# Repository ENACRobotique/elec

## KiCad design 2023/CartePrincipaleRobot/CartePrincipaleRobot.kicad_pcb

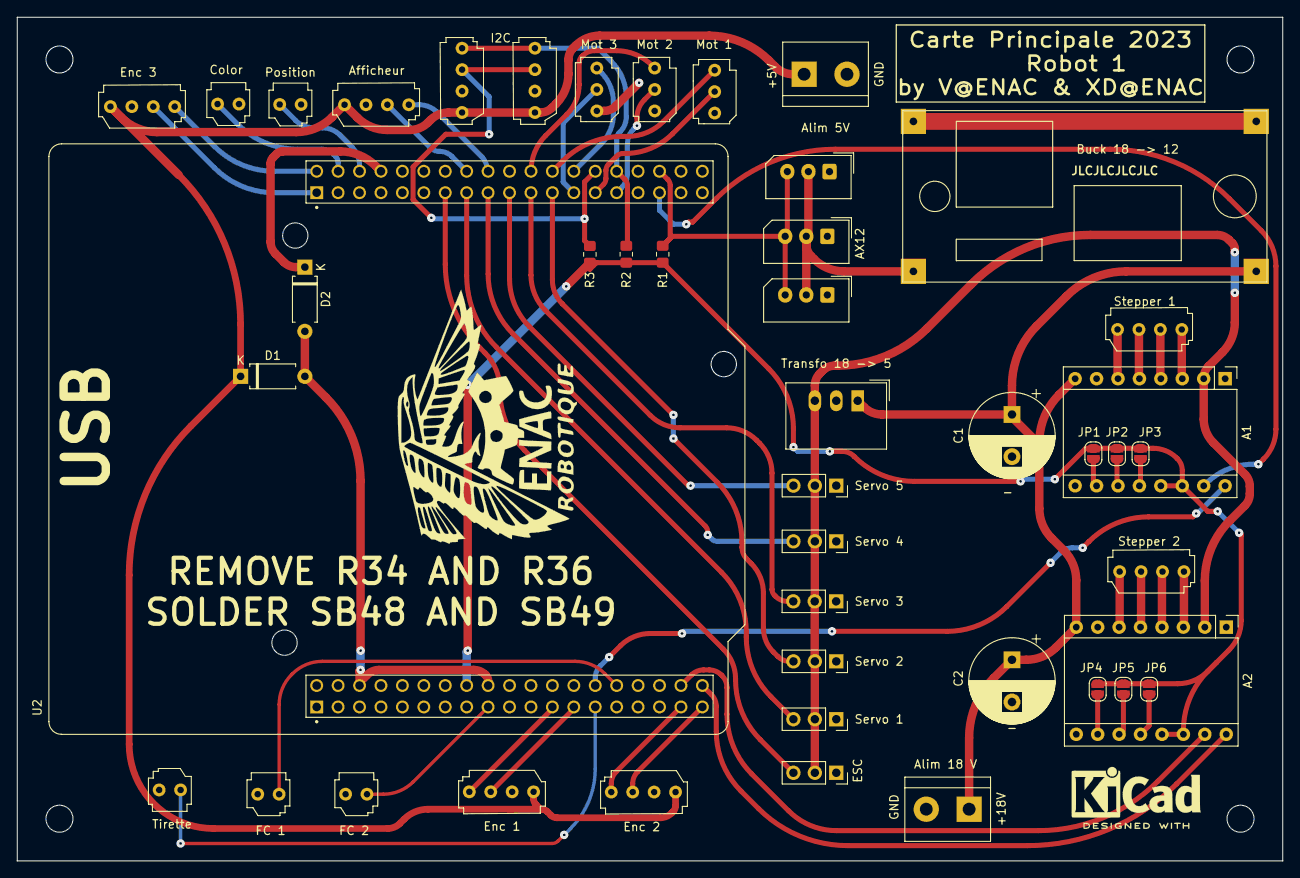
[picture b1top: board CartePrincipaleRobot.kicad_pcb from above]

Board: 2 copper layers, 150.0 x 100.0 mm, 45 parts (0 on the bottom side), 54 nets.

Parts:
A1, A2: Pololu_Breakout_A4988; Pololu_Breakout-16_15.2x20.3mm
AX12: Conn_01x03_Male; Molex_SPOX_5267-03A_1x03_P2.50mm_Vertical
Afficheur: Conn_01x04_Male; HE14_EMBASE_1x04
Alim 5V, Alim 18 V: Screw_Terminal_01x02; TerminalBlock_bornier-2_P5.08mm
Buck 18 -> 12: LM2596
C1, C2: 100µF; CP_Radial_D10.0mm_P5.00mm
Color: Conn_01x02_Male; HE14_EMBASE_1x02
D1, D2: DIODE; D_A-405_P7.62mm_Horizontal
ESC: Conn_01x03_Male; PinSocket_1x03_P2.54mm_Vertical
Enc 1, Enc 2, Enc 3: Conn_01x04_Male; HE14_EMBASE_1x04
FC 1, FC 2: Conn_01x02_Male; HE14_EMBASE_1x02
I2C: Conn_01x04_Male; HE14_EMBASE_1x04
J10, J11: Conn_01x03_Male; Molex_SPOX_5267-03A_1x03_P2.50mm_Vertical
J23: Conn_01x04_Male; HE14_EMBASE_1x04
JP1, JP2, JP3, JP4, JP5, JP6: SolderJumper_2_Open; SolderJumper-2_P1.3mm_Open_RoundedPad1.0x1.5mm
Mot 1, Mot 2, Mot 3: Conn_01x03_Male; HE14_EMBASE_1x03
Position: Conn_01x02_Male; HE14_EMBASE_1x02
R1: 1k; R_0805_2012Metric_Pad1.20x1.40mm_HandSolder
R2, R3: 2.2k; R_0805_2012Metric_Pad1.20x1.40mm_HandSolder
Servo 1, Servo 2, Servo 3, Servo 4, Servo 5: Conn_01x03_Male; PinSocket_1x03_P2.54mm_Vertical
Stepper 1, Stepper 2: Conn_01x04_Male; HE14_EMBASE_1x04
Tirette: Conn_01x02_Male; HE14_EMBASE_1x02
Transfo 18 -> 5: TSR_1-2450; Converter_DCDC_TRACO_TSR-1_THT
U2: NUCLEO-F476RG; ST_NUCLEO-F401RE

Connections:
5V_Logic: Afficheur.1, Alim 5V.1, D1.1 (K), Enc 1.1, Enc 2.1, Enc 3.1, I2C.1, J23.1
+3.3V: A1.13 (~RESET), A1.14 (~SLEEP), A2.13 (~RESET), A2.14 (~SLEEP), JP1.1 (A), JP2.1 (A), JP3.1 (A), JP4.1 (A), JP5.1 (A), JP6.1 (A), R1.1, R2.1, R3.1, U2.16 (+3V3)
+5V: A1.2 (VDD), A2.2 (VDD), ESC.2, Servo 1.2, Servo 2.2, Servo 3.2, Servo 4.2, Servo 5.2, Transfo 18 -> 5.3 (Vout)
+12V: AX12.2, Buck 18 -> 12.3 (OUT+), J10.2, J11.2
+18V: A1.8 (VMOT), A2.8 (VMOT), Alim 18 V.1, Buck 18 -> 12.1 (IN+), C1.1, C2.1, Transfo 18 -> 5.1 (Vin)
CLK_Afficheur: Afficheur.4, U2.56 (PB11)
Couleur: Color.1, U2.42 (PC6)
DIO_Afficheur: Afficheur.3, U2.54 (PB12)
ESC_PWM: ESC.3, U2.51 (PA6)
Enc1_A: Enc 1.3, U2.25 (PC14)
Enc1_B: Enc 1.4, U2.23 (PC13)
Enc2_A: Enc 2.3, U2.37 (PC3)
Enc2_B: Enc 2.4, U2.35 (PC2)
Enc3_A: Enc 3.3, U2.39 (PC9)
Enc3_B: Enc 3.4, U2.40 (PC8)
GND: A1.1 (GND), A1.7 (GND), A1.9 (~ENABLE), A2.1 (GND), A2.7 (GND), A2.9 (~ENABLE), AX12.1, Afficheur.2, Alim 5V.2, Alim 18 V.2, Buck 18 -> 12.2 (IN-), Buck 18 -> 12.4 (OUT-), C1.2, C2.2, Color.2, ESC.1, Enc 1.2, Enc 2.2, Enc 3.2, FC 1.1, FC 2.1, I2C.2, J10.1, J11.1, J23.2, Mot 1.1, Mot 2.1, Mot 3.1, Position.2, Servo 1.1, Servo 2.1, Servo 3.1, Servo 4.1, Servo 5.1, Tirette.2, Transfo 18 -> 5.2 (GND), U2.8 (GND), U2.19 (GND), U2.20 (GND), U2.22 (GND), U2.47 (GND), U2.58 (GND), U2.70 (AGND)
I2C_SCL: I2C.4, J23.4, R2.2, U2.68 (PB13)
I2C_SDA: I2C.3, J23.3, R3.2, U2.66 (PB14)
MOT1_DIR: Mot 1.3, U2.62 (PB1)
MOT1_PWM: Mot 1.2, U2.65 (PB4)
MOT2_DIR: Mot 2.3, U2.60 (PB2)
MOT2_PWM: Mot 2.2, U2.67 (PB5)
MOT3_DIR: Mot 3.3, U2.64 (PB15)
MOT3_PWM: Mot 3.2, U2.63 (PB10)
unnamed: A1.3 (1B), Stepper 1.4
unnamed: A1.4 (1A), Stepper 1.3
unnamed: A1.5 (2A), Stepper 1.2
unnamed: A1.6 (2B), Stepper 1.1
unnamed: A1.10 (MS1), JP1.2 (B)
unnamed: A1.11 (MS2), JP2.2 (B)
unnamed: A1.12 (MS3), JP3.2 (B)
unnamed: A2.3 (1B), Stepper 2.4
unnamed: A2.4 (1A), Stepper 2.3
unnamed: A2.5 (2A), Stepper 2.2
unnamed: A2.6 (2B), Stepper 2.1
unnamed: A2.10 (MS1), JP4.2 (B)
unnamed: A2.11 (MS2), JP5.2 (B)
unnamed: A2.12 (MS3), JP6.2 (B)
unnamed: D1.2 (A), D2.2 (A), U2.6 (E5V), U2.18 (+5V)
unnamed: D2.1 (K), U2.46 (U5V)
Position: Position.1, U2.44 (PC5)
Servo1: Servo 1.3, U2.53 (PA7)
Servo2: Servo 2.3, U2.61 (PA8)
Servo3: Servo 3.3, U2.59 (PA9)
Servo4: Servo 4.3, U2.55 (PB6)
Servo5: Servo 5.3, U2.57 (PC7)
Signal_AX12A: AX12.3, J10.3, J11.3, R1.2, U2.72 (PC4)
Stepper1_FinCourse: FC 1.2, U2.30 (PA1)
Stepper1_STP: A1.15 (STEP), U2.71 (PA10)
Stepper1_dir: A1.16 (DIR), U2.28 (PA0)
Stepper2_FinCourse: FC 2.2, U2.17 (PA15)
Stepper2_STP: A2.15 (STEP), U2.36 (PC1)
Stepper2_dir: A2.16 (DIR), U2.38 (PC0)
Tirette: Tirette.1, U2.27 (PC15)

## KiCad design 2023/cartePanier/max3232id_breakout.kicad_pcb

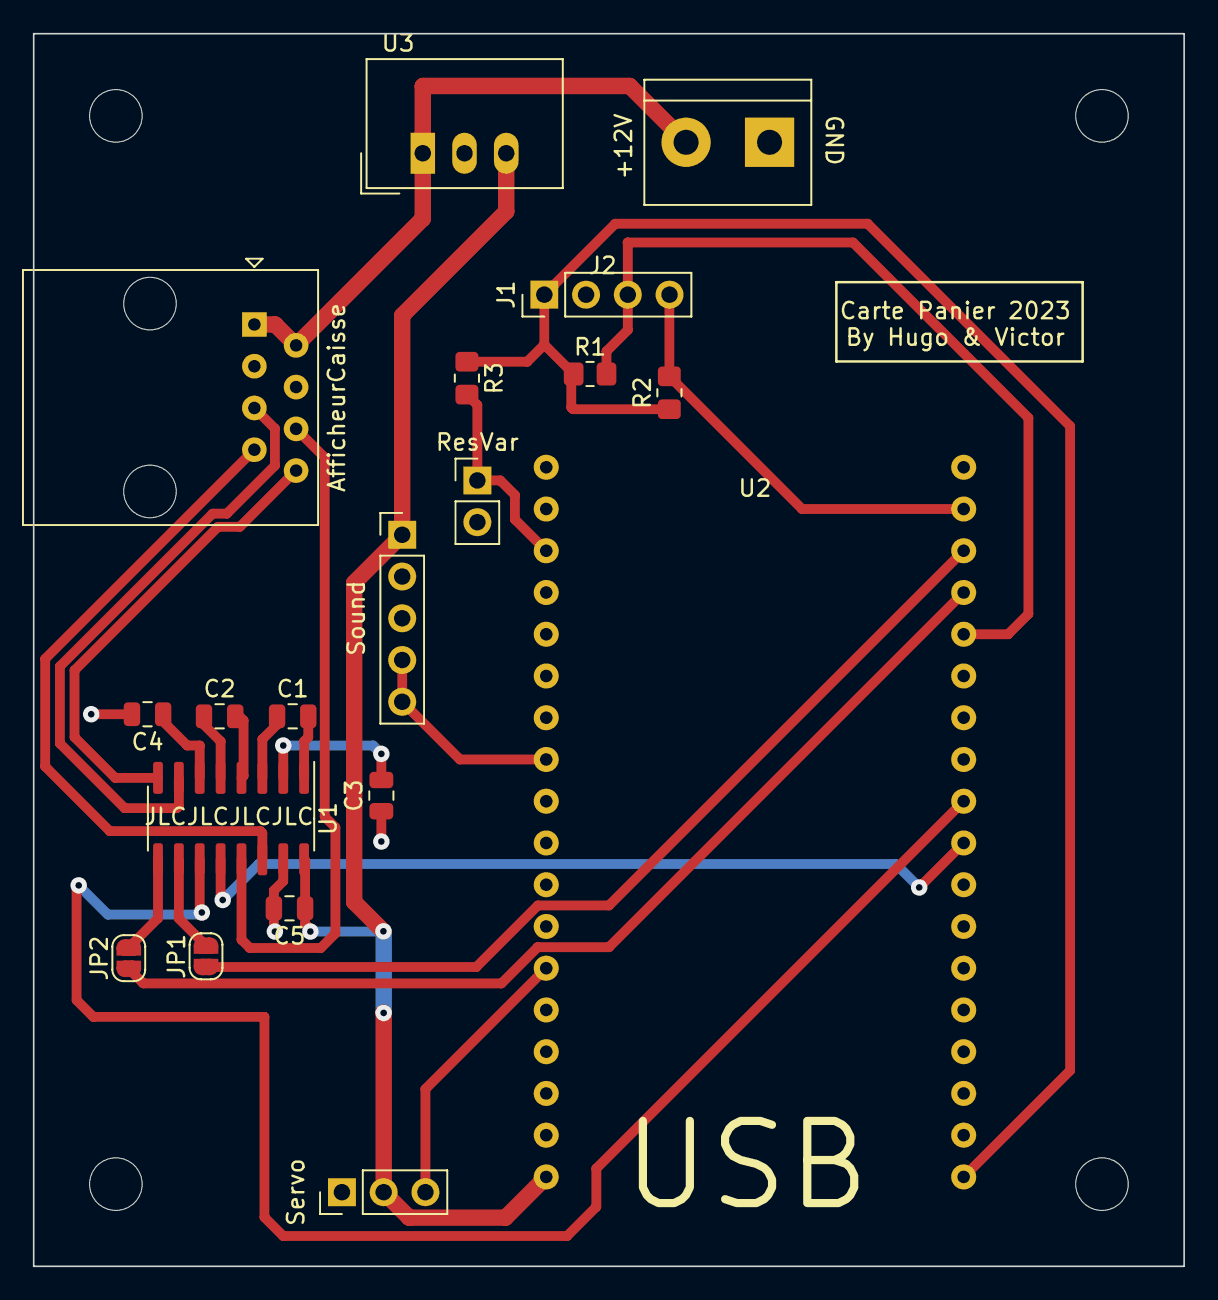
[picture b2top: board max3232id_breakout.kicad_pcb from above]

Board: 2 copper layers, 70.0 x 75.0 mm, 19 parts (0 on the bottom side), 25 nets.

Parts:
AfficheurCaisse: RJ45; RJ45_Amphenol_54602-x08_Horizontal
C1, C2, C3, C4, C5: 100n; C_0805_2012Metric
J1: Conn_01x04_Male; PinHeader_1x04_P2.54mm_Vertical
J2: Conn_01x02; TerminalBlock_bornier-2_P5.08mm
JP1, JP2: SolderJumper_2_Open; SolderJumper-2_P1.3mm_Open_RoundedPad1.0x1.5mm
R1, R2: R; R_0805_2012Metric_Pad1.20x1.40mm_HandSolder
R3: A Calculer; R_0805_2012Metric_Pad1.20x1.40mm_HandSolder
ResVar: Conn_01x02_Male; PinHeader_1x02_P2.54mm_Vertical
Servo: Conn_01x03_Male; PinHeader_1x03_P2.54mm_Vertical
Sound: Conn_01x05_Male; PinHeader_1x05_P2.54mm_Vertical
U1: MAX3232; SOIC-16_3.9x9.9mm_P1.27mm
U2: DOIT-ESP32-DEVKIT-V1; ESP32-DOIT-DEVKIT
U3: TSR_1-2450; Converter_DCDC_TRACO_TSR-1_THT

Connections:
+3.3V: J1.1, R1.1, R2.1, R3.1, U2.19 (3V3)
+5V: C5.1, Servo.2, Sound.1, U1.16 (VCC), U2.18 (VIN), U3.3 (Vout)
+12V: AfficheurCaisse.1, AfficheurCaisse.2, J2.2, U3.1 (Vin)
GND: AfficheurCaisse.3, AfficheurCaisse.4, C3.1, C4.2, C5.2, J1.2, J2.1, ResVar.2, Servo.1, Sound.2, Sound.3, U1.15 (GND), U2.17 (GND), U3.2 (GND)
I2C_SCL: J1.4, R2.2, U2.35 (GPIO22_I2C-SCL)
I2C_SDA: J1.3, R1.2, U2.32 (GPIO21_I2C-SDA)
LOGIC_IN1: U1.11 (T1IN), U2.28 (GPIO17_UART2-TX)
LOGIC_IN2: JP1.2 (B), U1.10 (T2IN)
LOGIC_OUT1: U1.12 (R1OUT), U2.27 (GPIO16_UART2-RX)
LOGIC_OUT2: JP2.2 (B), U1.9 (R2OUT)
MesurResVar: R3.2, ResVar.1, U2.3 (GPIO39_ADC1-CH3_SENS-VN_RTC-GPIO3)
unnamed: C1.1, U1.3 (C1-)
unnamed: C1.2, U1.1 (C1+)
unnamed: C2.1, U1.5 (C2-)
unnamed: C2.2, U1.4 (C2+)
unnamed: C3.2, U1.2 (VS+)
unnamed: C4.1, U1.6 (VS-)
unnamed: JP1.1 (A), U2.34 (GPIO1_UART0-TX)
unnamed: JP2.1 (A), U2.33 (GPIO3__UART0-RX)
RS232_IN1: AfficheurCaisse.6, U1.13 (R1IN)
RS232_IN2: AfficheurCaisse.8, U1.8 (R2IN)
RS232_OUT1: AfficheurCaisse.7, U1.14 (T1OUT)
RS232_OUT2: AfficheurCaisse.5, U1.7 (T2OUT)
SERVO: Servo.3, U2.13 (GPIO13_ADC2-CH4_HSPI-MOSI_RTC-GPIO14)
SOUND: Sound.4, Sound.5, U2.8 (GPIO25_ADC2-CH8_DAC1_RTC-GPIO6)

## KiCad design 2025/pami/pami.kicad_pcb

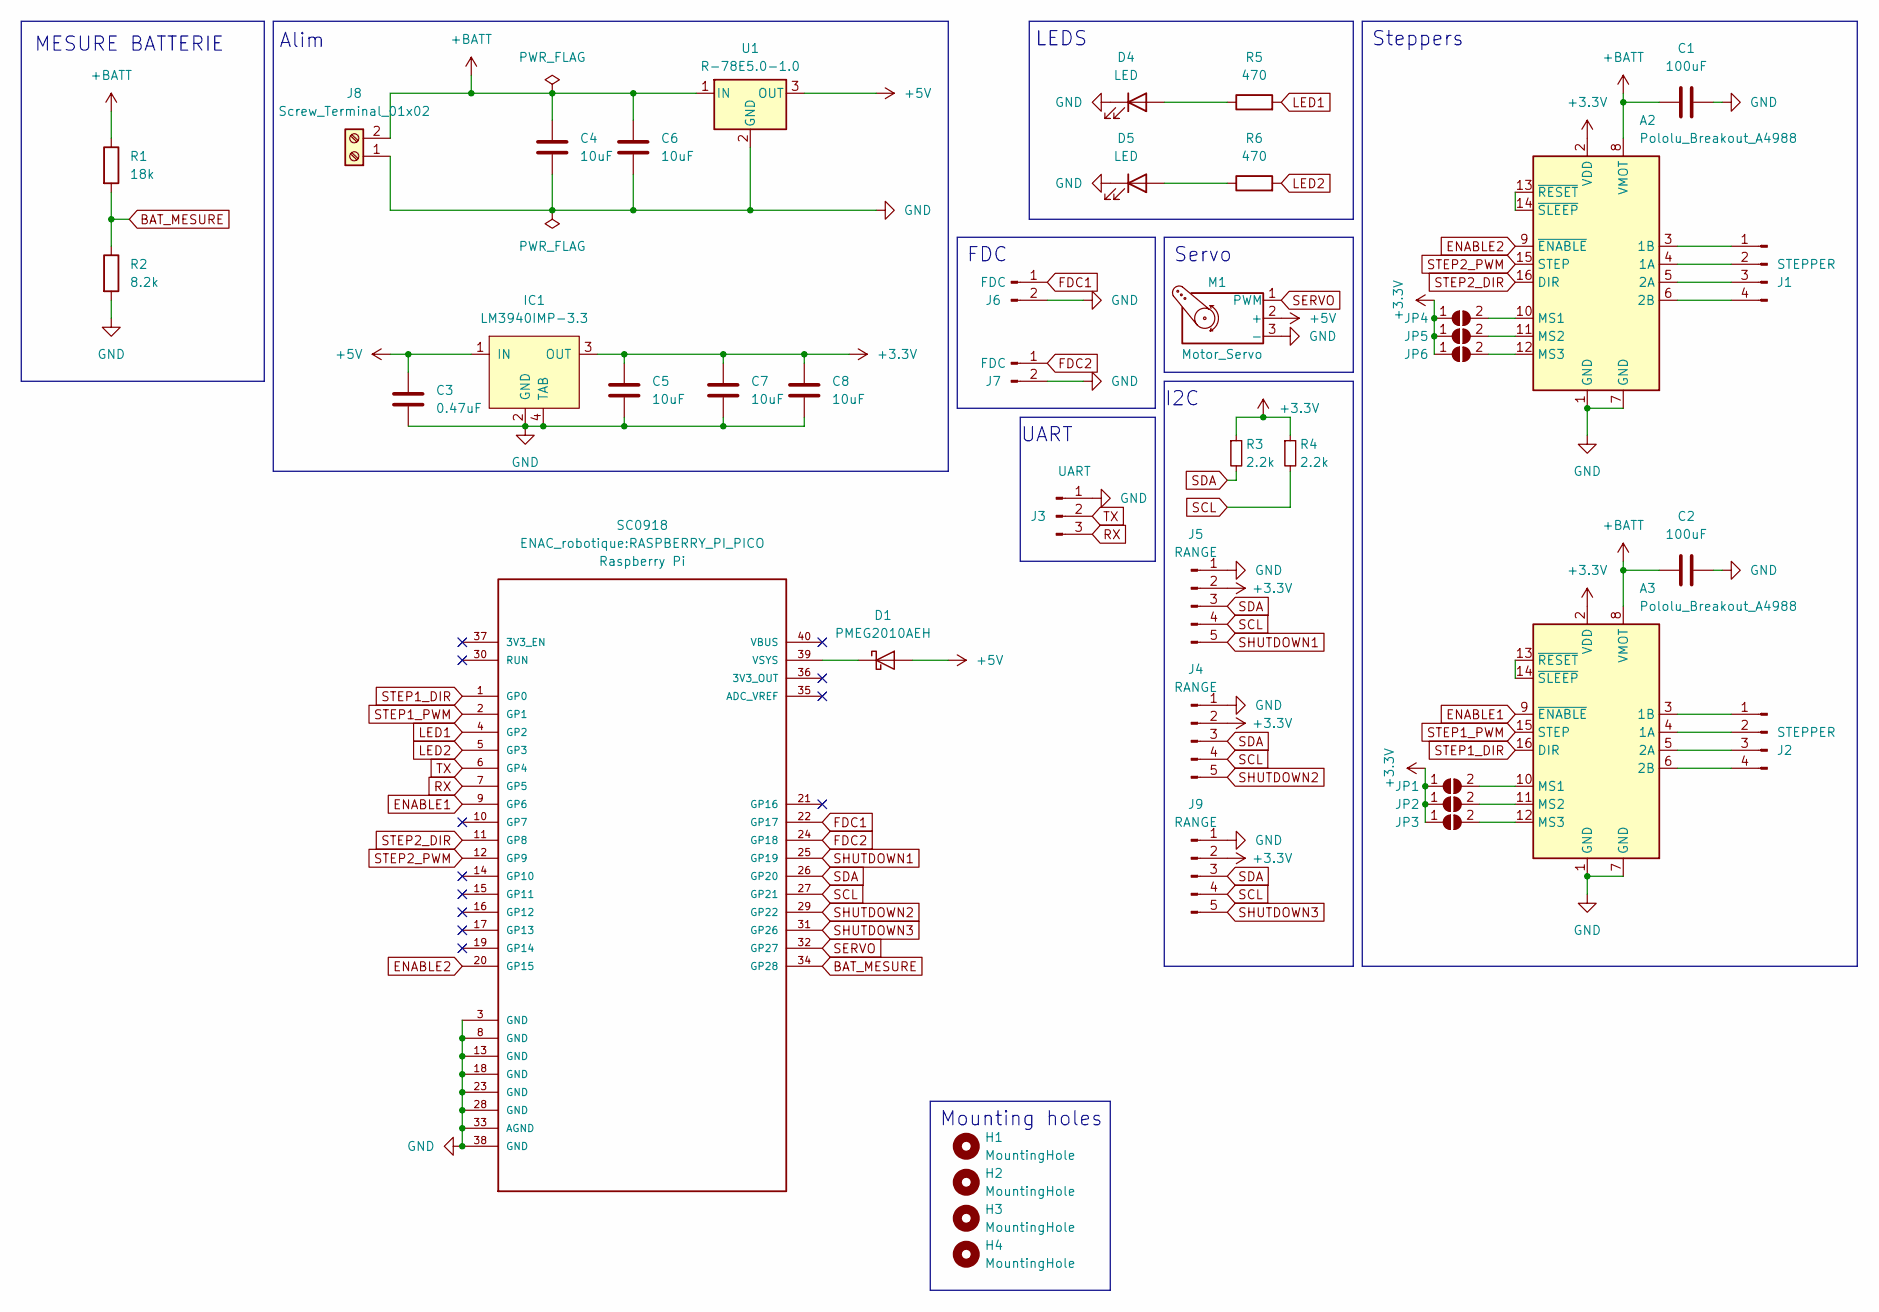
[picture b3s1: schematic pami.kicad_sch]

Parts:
A1: SC0918; RASPBERRY_PI_PICO; PARTREV 1.6
A2, A3: Pololu_Breakout_A4988; Pololu_Breakout-16_15.2x20.3mm
C1, C2: 100uF; CP_Elec_10x12.5
C3: 0.47uF; C_0805_2012Metric
C4, C5, C6, C7, C8: 10uF; C_0805_2012Metric
D1: PMEG2010AEH; D_SOD-123F
D4, D5: LED; LED_0603_1608Metric
H1, H2, H3, H4: MountingHole; MountingHole_3.2mm_M3
IC1: LM3940IMP-3.3; LM3940IMP
J1, J2: STEPPER; PinHeader_1x04_P2.54mm_Vertical
J3: UART; PinHeader_1x03_P2.54mm_Vertical
J4, J5, J9: RANGE; Molex_PicoBlade_53398-0571_1x05-1MP_P1.25mm_Vertical
J6, J7: FDC; PinHeader_1x02_P2.54mm_Vertical
J8: Screw_Terminal_01x02; TerminalBlock_bornier-2_P5.08mm
JP1, JP2, JP3, JP4, JP5, JP6: SolderJumper_2_Open; SolderJumper-2_P1.3mm_Open_TrianglePad1.0x1.5mm
M1: Motor_Servo; PinHeader_1x03_P2.54mm_Vertical
R1: 18k; R_0603_1608Metric
R2: 8.2k; R_0603_1608Metric
R3, R4: 2.2k; R_0805_2012Metric
R5, R6: 470; R_0603_1608Metric
U1: R-78E5.0-1.0; Converter_DCDC_RECOM_R-78E-0.5_THT

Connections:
+3.3V: A2.2 (VDD), A3.2 (VDD), C5.1, C7.1, C8.1, IC1.3 (OUT), J4.2, J5.2, J9.2, JP1.1 (A), JP2.1 (A), JP3.1 (A), JP4.1 (A), JP5.1 (A), JP6.1 (A), R3.1, R4.1
+5V: C3.1, D1.2 (A), IC1.1 (IN), M1.2 (+), U1.3 (OUT); also elsewhere on the board
+BATT: A2.8 (VMOT), A3.8 (VMOT), C1.1, C2.1, C4.2, C6.2, J8.2, R1.1, U1.1 (IN); also elsewhere on the board
BAT_MESURE: A1.34 (GP28), R1.2, R2.1
ENABLE1: A1.9 (GP6), A3.9 (~ENABLE)
ENABLE2: A1.20 (GP15), A2.9 (~ENABLE)
FDC1: A1.22 (GP17), J6.1; also elsewhere on the board
FDC2: A1.24 (GP18), J7.1; also elsewhere on the board
GND: A1.3 (GND), A1.8 (GND), A1.13 (GND), A1.18 (GND), A1.23 (GND), A1.28 (GND), A1.33 (AGND), A1.38 (GND), A2.1 (GND), A2.7 (GND), A3.1 (GND), A3.7 (GND), C1.2, C2.2, C3.2, C4.1, C5.2, C6.1, C7.2, C8.2, D4.1 (K), D5.1 (K), IC1.2 (GND), IC1.4 (TAB), J3.1, J4.1, J5.1, J6.2, J7.2, J8.1, J9.1, M1.3 (-), R2.2, U1.2 (GND); also elsewhere on the board
LED1: A1.4 (GP2), R5.2
LED2: A1.5 (GP3), R6.2
unnamed: A1.39 (VSYS), D1.1 (K)
unnamed: A2.4 (1A), J1.2
unnamed: A2.3 (1B), J1.1
unnamed: A2.5 (2A), J1.3
unnamed: A2.6 (2B), J1.4
unnamed: A2.10 (MS1), JP4.2 (B)
unnamed: A2.11 (MS2), JP5.2 (B)
unnamed: A2.12 (MS3), JP6.2 (B)
unnamed: A2.13 (~RESET), A2.14 (~SLEEP)
unnamed: A3.4 (1A), J2.2
unnamed: A3.3 (1B), J2.1
unnamed: A3.5 (2A), J2.3
unnamed: A3.6 (2B), J2.4
unnamed: A3.10 (MS1), JP1.2 (B)
unnamed: A3.11 (MS2), JP2.2 (B)
unnamed: A3.12 (MS3), JP3.2 (B)
unnamed: A3.13 (~RESET), A3.14 (~SLEEP)
unnamed: D4.2 (A), R5.1
unnamed: D5.2 (A), R6.1
RX: A1.7 (GP5), J3.3
SCL: A1.27 (GP21), J4.4, J5.4, J9.4, R4.2
SDA: A1.26 (GP20), J4.3, J5.3, J9.3, R3.2
SERVO: A1.32 (GP27), M1.1 (PWM)
SHUTDOWN1: A1.25 (GP19), J5.5
SHUTDOWN2: A1.29 (GP22), J4.5
SHUTDOWN3: A1.31 (GP26), J9.5
STEP1_DIR: A1.1 (GP0), A3.16 (DIR)
STEP1_PWM: A1.2 (GP1), A3.15 (STEP)
STEP2_DIR: A1.11 (GP8), A2.16 (DIR)
STEP2_PWM: A1.12 (GP9), A2.15 (STEP)
TX: A1.6 (GP4), J3.2

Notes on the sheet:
Steppers
FDC
I2C
LEDS
Alim
Servo
UART
Mounting holes
MESURE BATTERIE

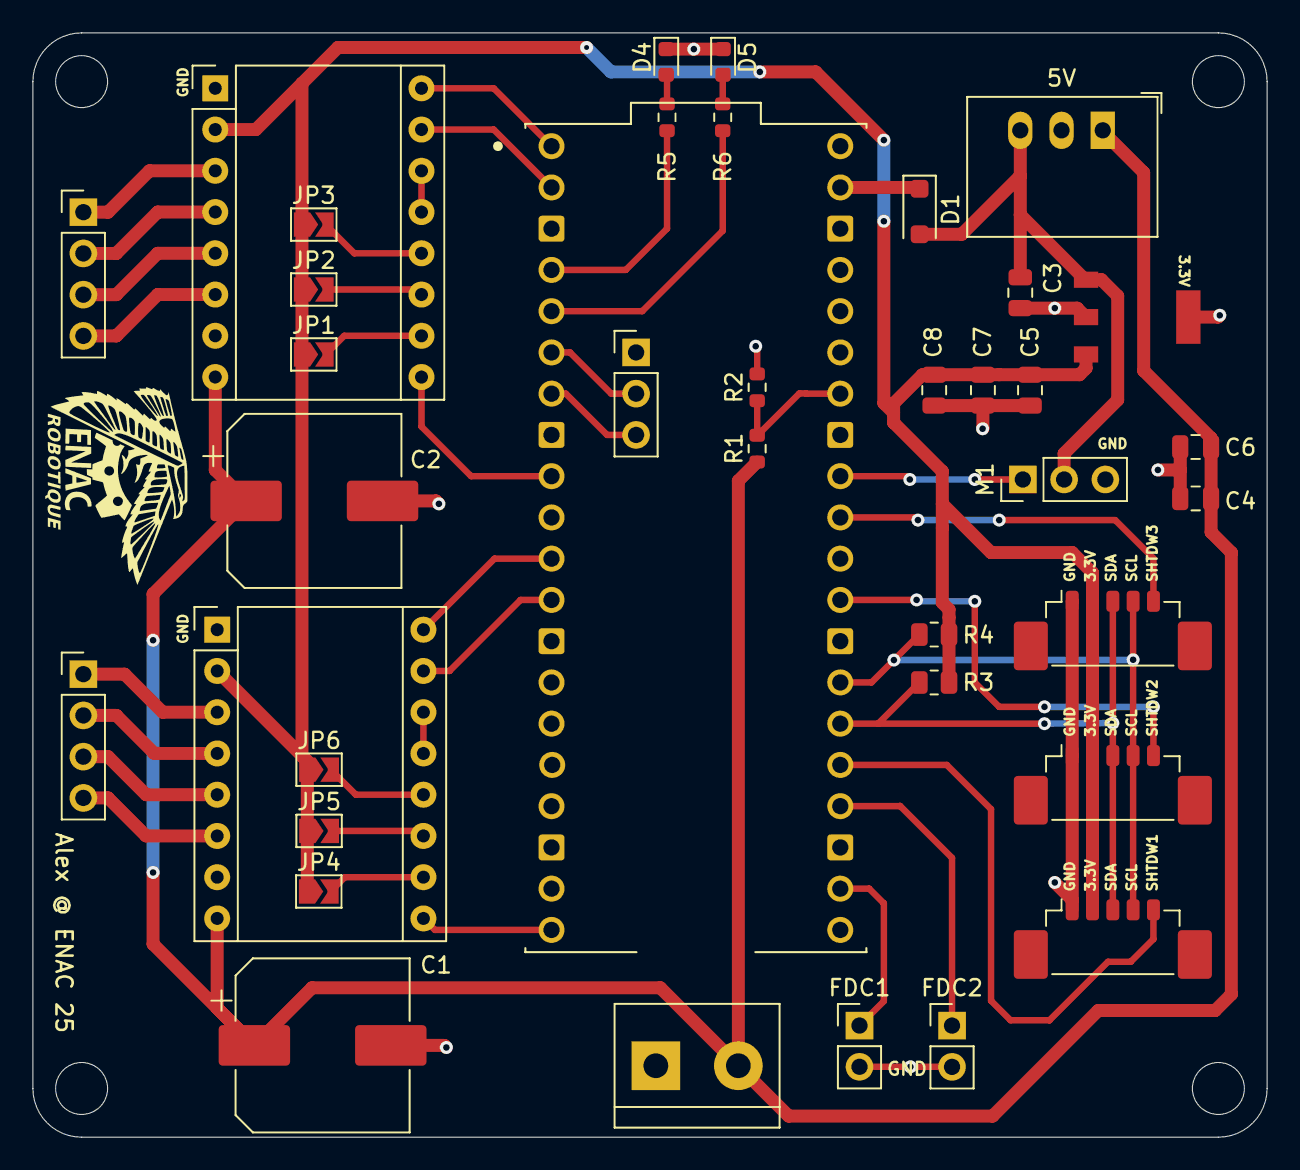
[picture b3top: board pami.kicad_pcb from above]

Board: 2 copper layers, 76.0 x 68.0 mm, 42 parts (0 on the bottom side), 42 nets.

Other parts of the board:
5V: R-78E5.0-1.0; Converter_DCDC_RECOM_R-78E-0.5_THT
FDC1, FDC2: FDC; PinHeader_1x02_P2.54mm_Vertical

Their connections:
+5V: 5V.3 (OUT); also elsewhere on the board
+BATT: 5V.1 (IN); also elsewhere on the board
FDC1: FDC1.1; also elsewhere on the board
FDC2: FDC2.1; also elsewhere on the board
GND: 5V.2 (GND), FDC1.2, FDC2.2; also elsewhere on the board

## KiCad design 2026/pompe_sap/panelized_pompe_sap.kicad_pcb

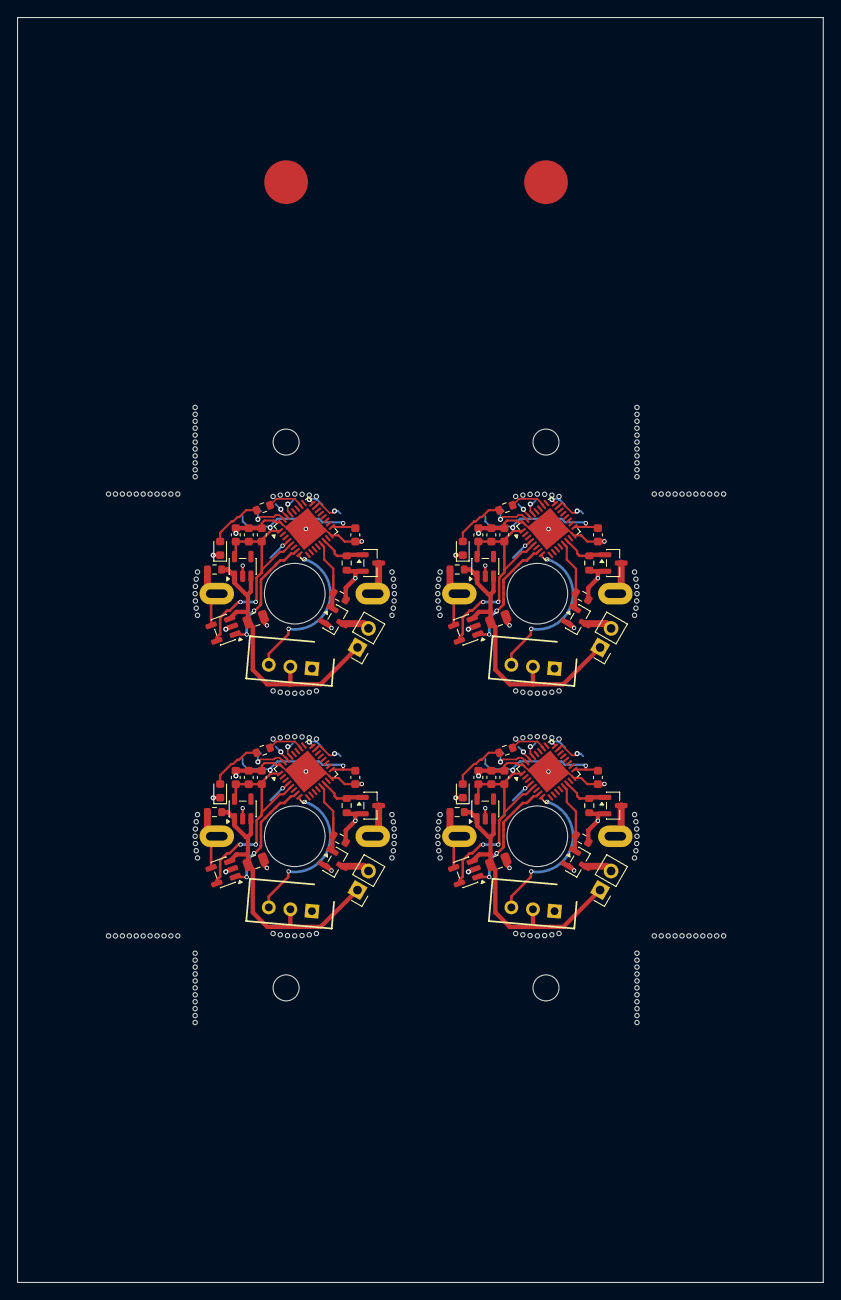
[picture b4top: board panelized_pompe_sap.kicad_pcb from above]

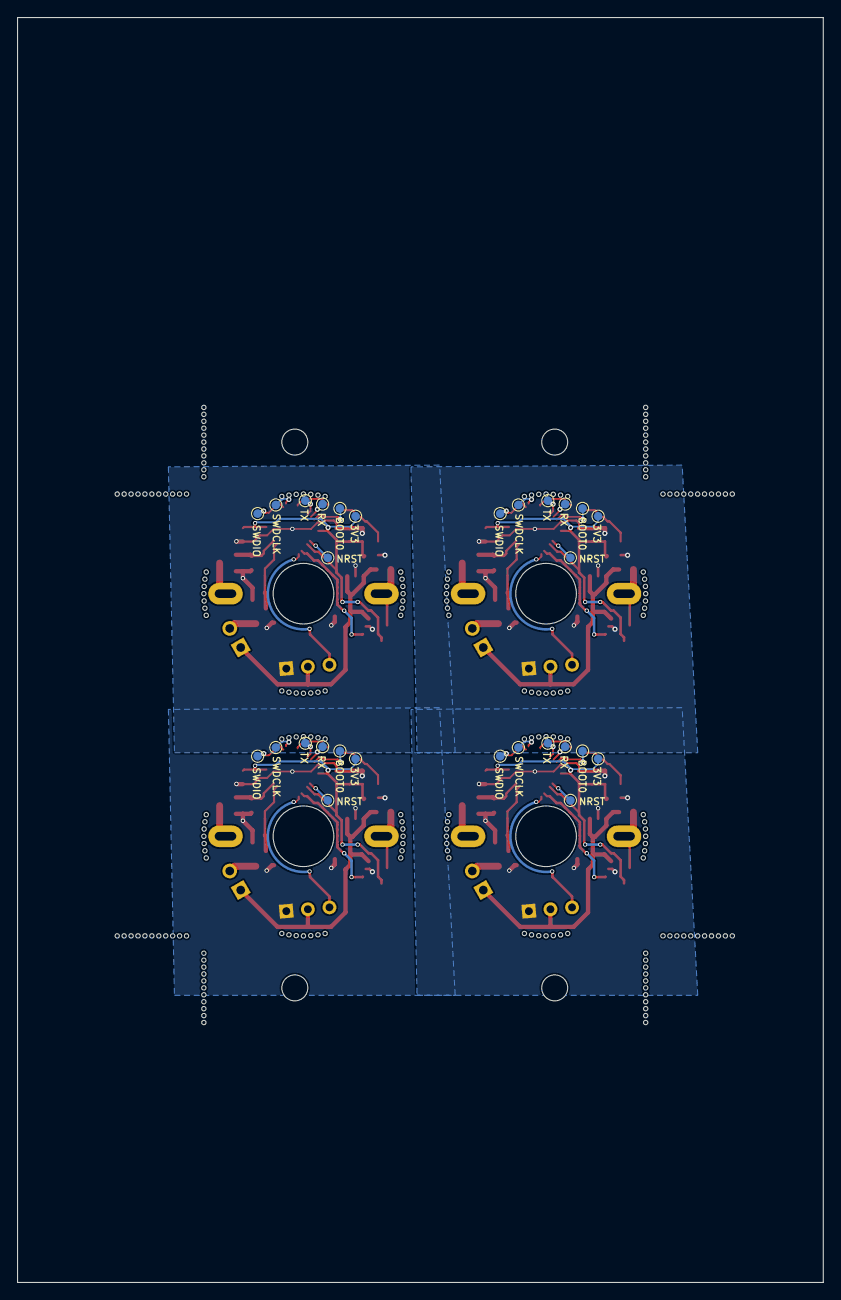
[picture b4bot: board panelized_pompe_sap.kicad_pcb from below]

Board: 2 copper layers, 93.0 x 146.0 mm, 304 parts (28 on the bottom side), 72 nets.

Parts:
C1, C1#2, C1#3, C1#4: C 1uf; C_0805_2012Metric
C2, C2#2, C2#3, C2#4: C 1uf; C_0603_1608Metric
C3, C3#2, C3#3, C3#4: 4U7; C_0603_1608Metric
C4, C4#2, C4#3, C4#4, C5, C5#2, C5#3, C5#4: 100n; C_0603_1608Metric
D1, D1#2, D1#3, D1#4: LED; LED_0603_1608Metric
J1, J1#2, J1#3, J1#4: Conn_01x02_Pin; PinHeader_1x02_P2.54mm_Vertical
J2, J2#2, J2#3, J2#4: 22-03-5035; SHDR3W70P0X250_1X3_990X490X590P
KiKit_MB_1_1, KiKit_MB_1_2, KiKit_MB_1_3, KiKit_MB_1_4, KiKit_MB_1_5, KiKit_MB_1_6, KiKit_MB_1_7, KiKit_MB_2_1, KiKit_MB_2_2, KiKit_MB_2_3, KiKit_MB_2_4, KiKit_MB_2_5, KiKit_MB_2_6, KiKit_MB_2_7, KiKit_MB_3_1, KiKit_MB_3_2, KiKit_MB_3_3, KiKit_MB_3_4, KiKit_MB_3_5, KiKit_MB_3_6, KiKit_MB_3_7, KiKit_MB_4_1, KiKit_MB_4_2, KiKit_MB_4_3, KiKit_MB_4_4, KiKit_MB_4_5, KiKit_MB_4_6, KiKit_MB_4_7, KiKit_MB_5_1, KiKit_MB_5_2, KiKit_MB_5_3, KiKit_MB_5_4, KiKit_MB_5_5, KiKit_MB_5_6, KiKit_MB_5_7, KiKit_MB_6_1, KiKit_MB_6_2, KiKit_MB_6_3, KiKit_MB_6_4, KiKit_MB_6_5, KiKit_MB_6_6, KiKit_MB_6_7, KiKit_MB_7_1, KiKit_MB_7_2, KiKit_MB_7_3, KiKit_MB_7_4, KiKit_MB_7_5, KiKit_MB_7_6, KiKit_MB_7_7, KiKit_MB_8_1, KiKit_MB_8_2, KiKit_MB_8_3, KiKit_MB_8_4, KiKit_MB_8_5, KiKit_MB_8_6, KiKit_MB_8_7, KiKit_MB_9_1, KiKit_MB_9_2, KiKit_MB_9_3, KiKit_MB_9_4, KiKit_MB_9_5, KiKit_MB_9_6, KiKit_MB_9_7, KiKit_MB_10_1, KiKit_MB_10_2, KiKit_MB_10_3, KiKit_MB_10_4, KiKit_MB_10_5, KiKit_MB_10_6, KiKit_MB_10_7, KiKit_MB_11_1, KiKit_MB_11_2, KiKit_MB_11_3, KiKit_MB_11_4, KiKit_MB_11_5, KiKit_MB_11_6, KiKit_MB_11_7, KiKit_MB_12_1, KiKit_MB_12_2, KiKit_MB_12_3, KiKit_MB_12_4, KiKit_MB_12_5, KiKit_MB_12_6, KiKit_MB_12_7, KiKit_MB_13_1, KiKit_MB_13_2, KiKit_MB_13_3, KiKit_MB_13_4, KiKit_MB_13_5, KiKit_MB_13_6, KiKit_MB_13_7, KiKit_MB_14_1, KiKit_MB_14_2, KiKit_MB_14_3, KiKit_MB_14_4, KiKit_MB_14_5, KiKit_MB_14_6, KiKit_MB_14_7, KiKit_MB_15_1, KiKit_MB_15_2, KiKit_MB_15_3, KiKit_MB_15_4, KiKit_MB_15_5, KiKit_MB_15_6, KiKit_MB_15_7, KiKit_MB_16_1, KiKit_MB_16_2, KiKit_MB_16_3, KiKit_MB_16_4, KiKit_MB_16_5, KiKit_MB_16_6, KiKit_MB_16_7, KiKit_MB_17_1, KiKit_MB_17_2, KiKit_MB_17_3, KiKit_MB_17_4, KiKit_MB_17_5, KiKit_MB_17_6, KiKit_MB_17_7, KiKit_MB_17_8, KiKit_MB_17_9, KiKit_MB_17_10, KiKit_MB_17_11, KiKit_MB_18_1, KiKit_MB_18_2, KiKit_MB_18_3, KiKit_MB_18_4, KiKit_MB_18_5, KiKit_MB_18_6, KiKit_MB_18_7, KiKit_MB_18_8, KiKit_MB_18_9, KiKit_MB_18_10, KiKit_MB_18_11, KiKit_MB_19_1, KiKit_MB_19_2, KiKit_MB_19_3, KiKit_MB_19_4, KiKit_MB_19_5, KiKit_MB_19_6, KiKit_MB_19_7, KiKit_MB_19_8, KiKit_MB_19_9, KiKit_MB_19_10, KiKit_MB_19_11, KiKit_MB_20_1, KiKit_MB_20_2, KiKit_MB_20_3, KiKit_MB_20_4, KiKit_MB_20_5, KiKit_MB_20_6, KiKit_MB_20_7, KiKit_MB_20_8, KiKit_MB_20_9, KiKit_MB_20_10, KiKit_MB_20_11, KiKit_MB_21_1, KiKit_MB_21_2, KiKit_MB_21_3, KiKit_MB_21_4, KiKit_MB_21_5, KiKit_MB_21_6, KiKit_MB_21_7, KiKit_MB_21_8, KiKit_MB_21_9, KiKit_MB_21_10, KiKit_MB_21_11, KiKit_MB_22_1, KiKit_MB_22_2, KiKit_MB_22_3, KiKit_MB_22_4, KiKit_MB_22_5, KiKit_MB_22_6, KiKit_MB_22_7, KiKit_MB_22_8, KiKit_MB_22_9, KiKit_MB_22_10, KiKit_MB_22_11, KiKit_MB_23_1, KiKit_MB_23_2, KiKit_MB_23_3, KiKit_MB_23_4, KiKit_MB_23_5, KiKit_MB_23_6, KiKit_MB_23_7, KiKit_MB_23_8, KiKit_MB_23_9, KiKit_MB_23_10, KiKit_MB_23_11, KiKit_MB_24_1, KiKit_MB_24_2, KiKit_MB_24_3, KiKit_MB_24_4, KiKit_MB_24_5, KiKit_MB_24_6, KiKit_MB_24_7, KiKit_MB_24_8, KiKit_MB_24_9, KiKit_MB_24_10, KiKit_MB_24_11: NPTH
KiKit_TO_1, KiKit_TO_2, KiKit_TO_3, KiKit_TO_4: NPTH
Q1, Q1#2, Q1#3, Q1#4, Q2, Q2#2, Q2#3, Q2#4: IRLML6344 (modèle du 6244); SOT-23
R1, R1#2, R1#3, R1#4: Rsens; R_0603_1608Metric
R2, R2#2, R2#3, R2#4: 390; R_0603_1608Metric
R4, R4#2, R4#3, R4#4, R5, R5#2, R5#3, R5#4: 100K; R_0603_1608Metric
TP1, TP1#2, TP1#3, TP1#4: SWDIO_TP; TestPoint_Pad_D1.0mm
TP2, TP2#2, TP2#3, TP2#4: SWDCLK_TP; TestPoint_Pad_D1.0mm
TP3, TP3#2, TP3#3, TP3#4: NRST_TP; TestPoint_Pad_D1.0mm
TP4, TP4#2, TP4#3, TP4#4: 3V3_TP; TestPoint_Pad_D1.0mm
TP5, TP5#2, TP5#3, TP5#4: BOOT0_TP; TestPoint_Pad_D1.0mm
TP6, TP6#2, TP6#3, TP6#4: U1_TX; TestPoint_Pad_D1.0mm
TP7, TP7#2, TP7#3, TP7#4: U1_RX; TestPoint_Pad_D1.0mm
U1, U1#2, U1#3, U1#4: pompe
U2, U2#2, U2#3, U2#4: NCP718xSN120; SOT-23-5
U3, U3#2, U3#3, U3#4: INA180A1; SOT-23-5
U4, U4#2, U4#3, U4#4: STM32L432KCUx; QFN-32-1EP_5x5mm_P0.5mm_EP3.45x3.45mm

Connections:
Board_0-+3V3: C2.1, C3#3.1, C4#2.1, C5#4.1, TP4#2.1, U2#3.5 (OUT), U3#4.5 (V+), U4#3.1 (VDD), U4#3.5 (VDDA), U4#3.17 (VDD)
Board_0-+12V: C1#4.1, J1#4.1, J2#2.2, R1#4.1, U2#3.1 (IN), U2#3.3 (EN), U3#4.3 (+)
Board_0-/BOOT0: TP5#4.1, U4#3.31 (PH3)
Board_0-/NRST: TP3#3.1, U4#3.4 (NRST)
Board_0-/SWDCLK: TP2#4.1, U4#3.24 (PA14)
Board_0-/SWDIO: TP1.1, U4#3.23 (PA13)
Board_0-GND: C1#4.2, C2.2, C3#3.2, C4#2.2, C5#4.2, D1#4.1 (K), J2#2.1, Q1#3.2 (S), Q2#3.2 (S), R4.2, R5.2, U2#3.2 (GND), U3#4.2 (GND), U4#3.16 (VSS), U4#3.32 (VSS), U4#3.33 (VSS)
Board_0-Net-(D1-A): D1#4.2 (A), R2#2.1
Board_0-Net-(J1-Pin_2): J1#4.2, Q2#3.3 (D)
Board_0-Net-(Q1-D): Q1#3.3 (D), U1#2.2
Board_0-Net-(U3--): R1#4.2, U1#2.1, U3#4.4 (-)
Board_0-Net-(U4-PB3): R2#2.2, U4#3.26 (PB3)
Board_0-Net-(U4-PB6): TP6#4.1, U4#3.29 (PB6)
Board_0-Net-(U4-PB7): TP7#4.1, U4#3.30 (PB7)
Board_0-PUMP: Q1#3.1 (G), R4.1, U4#3.14 (PB0)
Board_0-UART_TX: J2#2.3, U4#3.8 (PA2)
Board_0-VALVE: Q2#3.1 (G), R5.1, U4#3.13 (PA7)
Board_0-Vout: U3#4.1, U4#3.7 (PA1)
Board_1-+3V3: C2#2.1, C3.1, C4#3.1, C5#2.1, TP4.1, U2#2.5 (OUT), U3#2.5 (V+), U4#2.1 (VDD), U4#2.5 (VDDA), U4#2.17 (VDD)
Board_1-+12V: C1.1, J1#3.1, J2#4.2, R1.1, U2#2.1 (IN), U2#2.3 (EN), U3#2.3 (+)
Board_1-/BOOT0: TP5#2.1, U4#2.31 (PH3)
Board_1-/NRST: TP3.1, U4#2.4 (NRST)
Board_1-/SWDCLK: TP2#3.1, U4#2.24 (PA14)
Board_1-/SWDIO: TP1#3.1, U4#2.23 (PA13)
Board_1-GND: C1.2, C2#2.2, C3.2, C4#3.2, C5#2.2, D1#2.1 (K), J2#4.1, Q1#2.2 (S), Q2#4.2 (S), R4#3.2, R5#3.2, U2#2.2 (GND), U3#2.2 (GND), U4#2.16 (VSS), U4#2.32 (VSS), U4#2.33 (VSS)
Board_1-Net-(D1-A): D1#2.2 (A), R2#4.1
Board_1-Net-(J1-Pin_2): J1#3.2, Q2#4.3 (D)
Board_1-Net-(Q1-D): Q1#2.3 (D), U1.2
Board_1-Net-(U3--): R1.2, U1.1, U3#2.4 (-)
Board_1-Net-(U4-PB3): R2#4.2, U4#2.26 (PB3)
Board_1-Net-(U4-PB6): TP6#2.1, U4#2.29 (PB6)
Board_1-Net-(U4-PB7): TP7#3.1, U4#2.30 (PB7)
Board_1-PUMP: Q1#2.1 (G), R4#3.1, U4#2.14 (PB0)
Board_1-UART_TX: J2#4.3, U4#2.8 (PA2)
Board_1-VALVE: Q2#4.1 (G), R5#3.1, U4#2.13 (PA7)
Board_1-Vout: U3#2.1, U4#2.7 (PA1)
Board_2-+3V3: C2#4.1, C3#4.1, C4#4.1, C5.1, TP4#3.1, U2#4.5 (OUT), U3.5 (V+), U4#4.1 (VDD), U4#4.5 (VDDA), U4#4.17 (VDD)
Board_2-+12V: C1#2.1, J1#2.1, J2.2, R1#3.1, U2#4.1 (IN), U2#4.3 (EN), U3.3 (+)
Board_2-/BOOT0: TP5#3.1, U4#4.31 (PH3)
Board_2-/NRST: TP3#4.1, U4#4.4 (NRST)
Board_2-/SWDCLK: TP2#2.1, U4#4.24 (PA14)
Board_2-/SWDIO: TP1#2.1, U4#4.23 (PA13)
Board_2-GND: C1#2.2, C2#4.2, C3#4.2, C4#4.2, C5.2, D1#3.1 (K), J2.1, Q1#4.2 (S), Q2.2 (S), R4#4.2, R5#4.2, U2#4.2 (GND), U3.2 (GND), U4#4.16 (VSS), U4#4.32 (VSS), U4#4.33 (VSS)
Board_2-Net-(D1-A): D1#3.2 (A), R2#3.1
Board_2-Net-(J1-Pin_2): J1#2.2, Q2.3 (D)
Board_2-Net-(Q1-D): Q1#4.3 (D), U1#3.2
Board_2-Net-(U3--): R1#3.2, U1#3.1, U3.4 (-)
Board_2-Net-(U4-PB3): R2#3.2, U4#4.26 (PB3)
Board_2-Net-(U4-PB6): TP6.1, U4#4.29 (PB6)
Board_2-Net-(U4-PB7): TP7.1, U4#4.30 (PB7)
Board_2-PUMP: Q1#4.1 (G), R4#4.1, U4#4.14 (PB0)
Board_2-UART_TX: J2.3, U4#4.8 (PA2)
Board_2-VALVE: Q2.1 (G), R5#4.1, U4#4.13 (PA7)
Board_2-Vout: U3.1, U4#4.7 (PA1)
Board_3-+3V3: C2#3.1, C3#2.1, C4.1, C5#3.1, TP4#4.1, U2.5 (OUT), U3#3.5 (V+), U4.1 (VDD), U4.5 (VDDA), U4.17 (VDD)
Board_3-+12V: C1#3.1, J1.1, J2#3.2, R1#2.1, U2.1 (IN), U2.3 (EN), U3#3.3 (+)
Board_3-/BOOT0: TP5.1, U4.31 (PH3)
Board_3-/NRST: TP3#2.1, U4.4 (NRST)
Board_3-/SWDCLK: TP2.1, U4.24 (PA14)
Board_3-/SWDIO: TP1#4.1, U4.23 (PA13)
Board_3-GND: C1#3.2, C2#3.2, C3#2.2, C4.2, C5#3.2, D1.1 (K), J2#3.1, Q1.2 (S), Q2#2.2 (S), R4#2.2, R5#2.2, U2.2 (GND), U3#3.2 (GND), U4.16 (VSS), U4.32 (VSS), U4.33 (VSS)
Board_3-Net-(D1-A): D1.2 (A), R2.1
Board_3-Net-(J1-Pin_2): J1.2, Q2#2.3 (D)
Board_3-Net-(Q1-D): Q1.3 (D), U1#4.2
Board_3-Net-(U3--): R1#2.2, U1#4.1, U3#3.4 (-)
Board_3-Net-(U4-PB3): R2.2, U4.26 (PB3)
Board_3-Net-(U4-PB6): TP6#3.1, U4.29 (PB6)
Board_3-Net-(U4-PB7): TP7#2.1, U4.30 (PB7)
Board_3-PUMP: Q1.1 (G), R4#2.1, U4.14 (PB0)
Board_3-UART_TX: J2#3.3, U4.8 (PA2)
Board_3-VALVE: Q2#2.1 (G), R5#2.1, U4.13 (PA7)
Board_3-Vout: U3#3.1, U4.7 (PA1)
